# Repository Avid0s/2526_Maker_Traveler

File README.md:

# 25-26_Maker_Traveler
Gabriel VIDON\
Projet d'option Maker à l'ENSEA.

# Vidéo :
Version 1 min 30 :\
https://youtu.be/IOBbxCDs6Es

Version 1 min 45 : (une étape en plus)\
https://youtu.be/CtQkx19j3xo

# 1 Description du projet

## 1.1 Contexte

J'ai toujours été passioné par la robotique et les systèmes embarqués, c'est pour cela que dans le cadre d'un projet Maker qui devait regrouper le plus de technologies possibles pour apprendre leur fonctionnement. J'ai décidé de travailler sur un projet de voiture téléguidée par connection bluetooth. Pour éviter de devoir créer un système de rotation pour les roues de zero, j'ai décidé d'utiliser des roues holonomes.\ 
Ce système qui deverait toucher à toutes les technologies d'impression 3D, de découpe laser, routage pcb, et toutes les autres vues en cours de Maker.
Mes objectifs sont les suivants :
- Créer un chassis pouvant supporter l'ensemble du système
- Créer un PCB avec un ESP32 permettant de controler les moteurs
- Créer un programme permettant de communiquer en bluetooth avec l'ESP et de controler la voiture depuis un telephone puis une manette.

## 1.2 Retroplanning

| Séance | Objectif|
|--------|---------|
|TP1     |Définir les spécifications, choisir les composants, rédiger le cahier des charges et planifier les tâches.|
|TP2     |Modéliser le châssis en 3D, concevoir le schéma du PCB et préparer les fichiers pour la fabrication.|
|TP3     |Imprimer/découper le châssis, finaliser le PCB et préparer les outils pour la séance suivante.|
|TP4     |Souder les composants sur le PCB et écrire le code de base pour contrôler les moteurs.|
|TP5     |Développer la communication Bluetooth et tester les mouvements de la voiture.|
|TP6     |Assembler le châssis, tester l'ensemble (mouvements, Bluetooth) et finaliser le code.|
|TP7     |Valider les tests, rédiger le rapport technique et préparer la démonstration.|

# 2 Projet

## Séance 1

L'alimentation de la voiture sera fait grâce a une batterie 12v, cette tension sera convertie en 5v par un convertisseur DC-DC, qui alimentera toute la carte.\
Un esp32 recuperera les informations de mouvement depuis une connection bluetooth, enverra la PWM appropriée aux drivers, qui eux controleront les moteurs.\
Les moteurs seront eux alimentés par la batterie 12v, et leur valeur d'encodeur sera renvoyée à l'esp pour permettre un niveau de précision adéquat pour utiliser les roues omnidirectionelles.\
Une interface sera faite sur telephone avec l'application BT electronics, et si le temps le permets, le robot sera controlé par une manette de ps4

| Composant | Référence | Lien | Quantité |
|-----------|-----------|------|----------|
| Moteurs | FIT0520 | [https://www.dfrobot.com/product-1619.html](https://www.dfrobot.com/product-1619.html)| x4 |
| Drivers moteur | DRV8411APWPR | | x2 |
| ESP32 | | | x1 |
| Roues omnidirectionelles | FIT0779 | [https://www.gotronic.fr/art-roue-omnidirectionnelle-droite-fit0780-34179.htm](https://www.gotronic.fr/art-roue-omnidirectionnelle-droite-fit0780-34179.htm) | x2L x2R |
| Convertisseur 6v-5v | 171013801 | [https://www.we-online.com/components/products/datasheet/171013801.pdf](https://www.we-online.com/components/products/datasheet/171013801.pdf) | x1 |
| Batterie 6v | fait in ensea |  | x1 |

Lien Onshape :\
[https://cad.onshape.com/documents/018aeca4da422949587763ea/w/2b34d823b7b37a4e9442f19b/e/016c48b2dd776d725fede060](https://cad.onshape.com/documents/018aeca4da422949587763ea/w/2b34d823b7b37a4e9442f19b/e/016c48b2dd776d725fede060)

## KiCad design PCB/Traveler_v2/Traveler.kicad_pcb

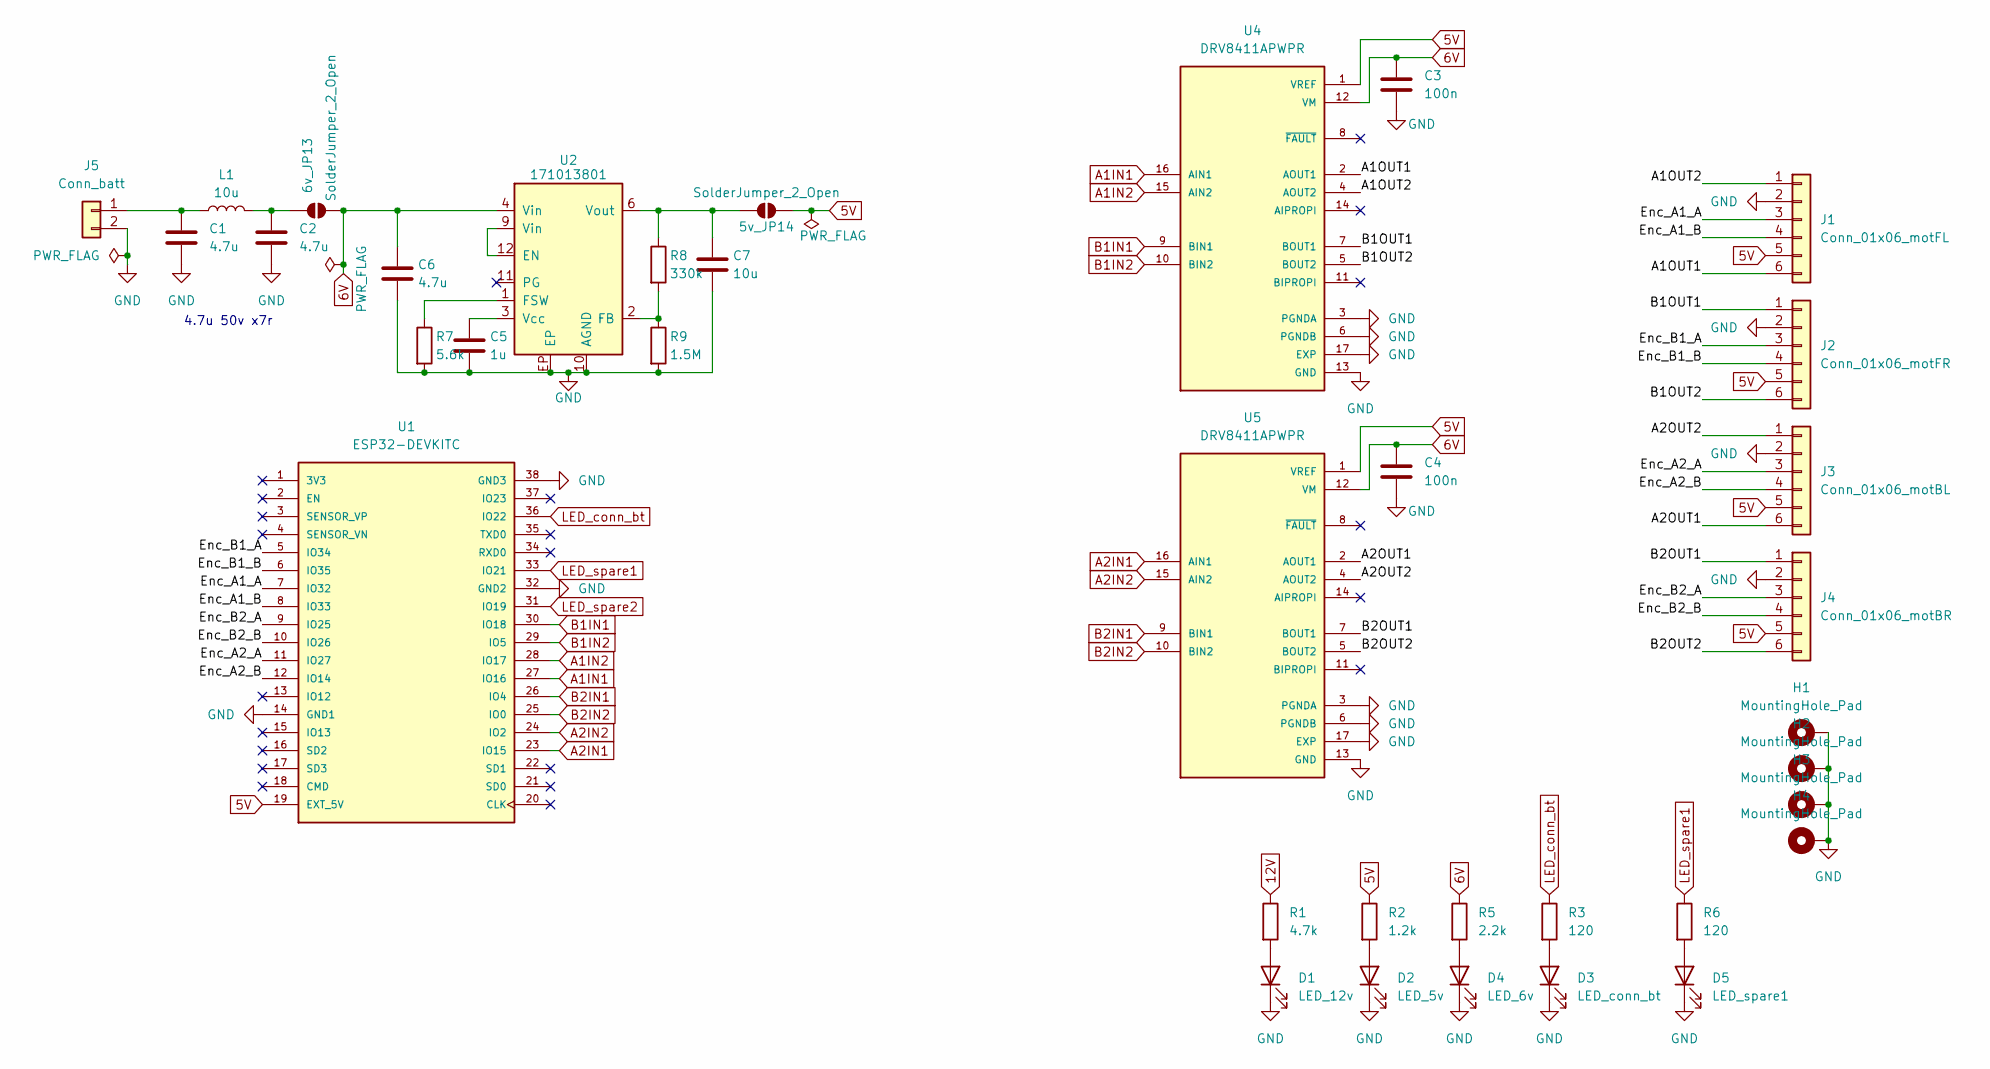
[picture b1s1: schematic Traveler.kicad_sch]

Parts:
5v_JP14, 6v_JP13: SolderJumper_2_Open; SolderJumper-2_P1.3mm_Open_TrianglePad1.0x1.5mm
C1, C2, C6: 4.7u; C_0603_1608Metric
C3, C4: 100n; C_0603_1608Metric
C5: 1u; C_0603_1608Metric
C7: 10u; C_0603_1608Metric
D1: LED_12v; LED_0603_1608Metric_Pad1.05x0.95mm_HandSolder
D2: LED_5v; LED_0603_1608Metric_Pad1.05x0.95mm_HandSolder
D3: LED_conn_bt; LED_0603_1608Metric_Pad1.05x0.95mm_HandSolder
D4: LED_6v; LED_0603_1608Metric_Pad1.05x0.95mm_HandSolder
D5: LED_spare1; LED_0603_1608Metric_Pad1.05x0.95mm_HandSolder
H1, H2, H3, H4: MountingHole_Pad; MountingHole_2.7mm_Pad_TopBottom
J1: Conn_01x06_motFL; PinHeader_1x06_P2.54mm_Vertical
J2: Conn_01x06_motFR; PinHeader_1x06_P2.54mm_Vertical
J3: Conn_01x06_motBL; PinHeader_1x06_P2.54mm_Vertical
J4: Conn_01x06_motBR; PinHeader_1x06_P2.54mm_Vertical
J5: Conn_batt; JST_EH_B2B-EH-A_1x02_P2.50mm_Vertical
L1: 10u; capa1
R1: 4.7k; R_0603_1608Metric
R2: 1.2k; R_0603_1608Metric
R3, R6: 120; R_0603_1608Metric
R5: 2.2k; R_0603_1608Metric
R7: 5.6k; R_0603_1608Metric
R8: 330k; R_0603_1608Metric
R9: 1.5M; R_0603_1608Metric
U1: ESP32-DEVKITC; MODULE_ESP32-DEVKITC; PARTREV N/A
U2: 171013801; WPME-VDLM_LGA-12EP
U4, U5: DRV8411APWPR; IC_DRV8411APWPR; PARTREV A

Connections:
5V: 5v_JP14.2 (B), J1.5, J2.5, J3.5, J4.5, R2.1, U1.19 (EXT_5V), U4.1 (VREF), U5.1 (VREF)
6V: 6v_JP13.2 (B), C3.1, C4.1, C6.1, R5.1, U2.4 (Vin), U2.5 (Vin), U4.12 (VM), U5.12 (VM)
12V: R1.1
/A1OUT1: J1.6, U4.2 (AOUT1)
/A1OUT2: J1.1, U4.4 (AOUT2)
/A2OUT1: J3.6, U5.2 (AOUT1)
/A2OUT2: J3.1, U5.4 (AOUT2)
/B1OUT1: J2.1, U4.7 (BOUT1)
/B1OUT2: J2.6, U4.5 (BOUT2)
/B2OUT1: J4.1, U5.7 (BOUT1)
/B2OUT2: J4.6, U5.5 (BOUT2)
/Enc_A1_A: J1.3, U1.7 (IO32)
/Enc_A1_B: J1.4, U1.8 (IO33)
/Enc_A2_A: J3.3, U1.11 (IO27)
/Enc_A2_B: J3.4, U1.12 (IO14)
/Enc_B1_A: J2.3, U1.5 (IO34)
/Enc_B1_B: J2.4, U1.6 (IO35)
/Enc_B2_A: J4.3, U1.9 (IO25)
/Enc_B2_B: J4.4, U1.10 (IO26)
A1IN1: U1.27 (IO16), U4.16 (AIN1)
A1IN2: U1.28 (IO17), U4.15 (AIN2)
A2IN1: U1.23 (IO15), U5.16 (AIN1)
A2IN2: U1.24 (IO2), U5.15 (AIN2)
B1IN1: U1.30 (IO18), U4.9 (BIN1)
B1IN2: U1.29 (IO5), U4.10 (BIN2)
B2IN1: U1.26 (IO4), U5.9 (BIN1)
B2IN2: U1.25 (IO0), U5.10 (BIN2)
GND: C1.2, C2.2, C3.2, C4.2, C5.2, C6.2, C7.2, D1.1 (K), D2.1 (K), D3.1 (K), D4.1 (K), D5.1 (K), H1.1, H2.1, H3.1, H4.1, J1.2, J2.2, J3.2, J4.2, J5.2, R7.2, R9.2, U1.14 (GND1), U1.32 (GND2), U1.38 (GND3), U2.10 (AGND), U2.EP, U4.3 (PGNDA), U4.6 (PGNDB), U4.13 (GND), U4.17 (EXP), U5.3 (PGNDA), U5.6 (PGNDB), U5.13 (GND), U5.17 (EXP)
LED_conn_bt: R3.1, U1.36 (IO22)
LED_spare1: R6.1, U1.33 (IO21)
LED_spare2: U1.31 (IO19)
unnamed: 6v_JP13.1 (A), C2.1, L1.2
unnamed: D1.2 (A), R1.2
unnamed: D2.2 (A), R2.2
unnamed: D3.2 (A), R3.2
unnamed: D4.2 (A), R5.2
unnamed: D5.2 (A), R6.2
unnamed: C1.1, J5.1, L1.1
unnamed: U2.9 (Vin), U2.12 (EN)
unnamed: R8.2, R9.1, U2.2 (FB)
unnamed: R7.1, U2.1 (FSW)
unnamed: C5.1, U2.3 (Vcc)
Vout: 5v_JP14.1 (A), C7.1, R8.1, U2.6 (Vout), U2.7 (Vout)

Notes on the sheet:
4.7u 50v x7r

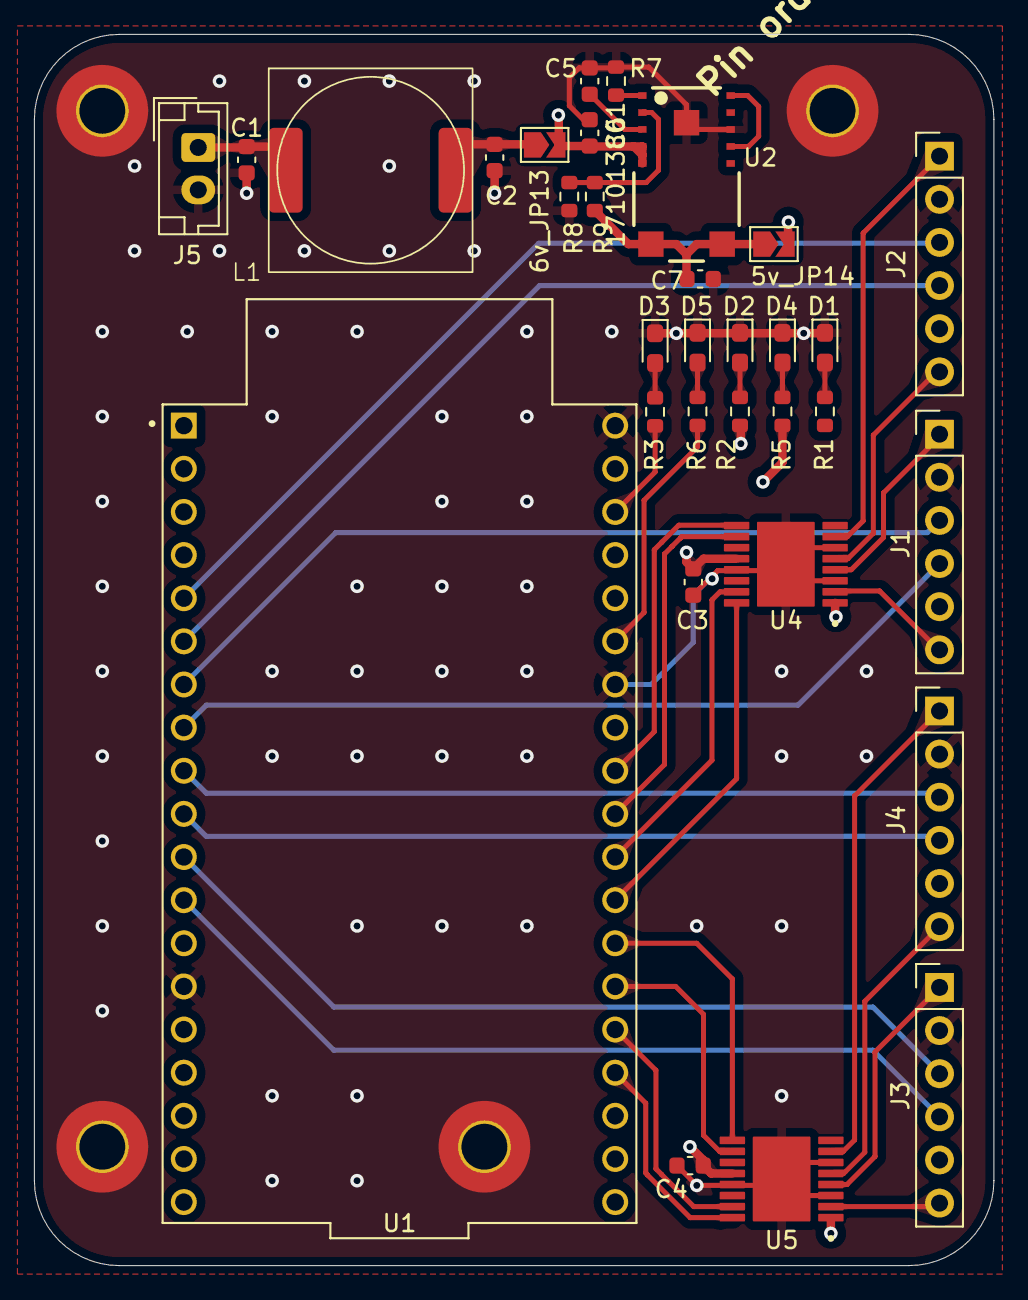
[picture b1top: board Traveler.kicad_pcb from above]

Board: 4 copper layers, 56.5 x 72.5 mm, 36 parts (0 on the bottom side), 41 nets.

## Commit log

2026-01-15 Initial readme txt
2026-01-19 update description
2026-01-19 mise en forme + nom
2026-01-22 added context and retroplanning
2026-01-22 Update project title formatting in README
2026-02-16 Added séance 1
    Added project details including power supply, motor control, and components list.
2026-03-09 added ref driver moteur
2026-03-09 début schéma elec pcb
    recherches sur moteurs, drivers, esp and more
2026-03-19 Finition de pcb, prèt pour verification
2026-03-23 Changed component
2026-03-23 Vers 2 couches
    A créer : une vers 4 couches, remplacer batt 12v vers 6v pour alim directement depuis batt
2026-03-23 changements schematic elec pour une batt 6v
    a faire, routage :(
2026-03-23 Finition PCB et envoi vers fabrication
2026-03-24 fichiers gerber et suppression backups
2026-03-30 cration of cad pcb file
2026-03-30 changement composants vers mot 6V + rajout liens
2026-03-30 lien onshape
2026-04-02 Remove Traveler.cad; add backups, STL, lock
    Delete the large Traveler.cad export and update the KiCad project metadata. Add two backup ZIPs in PCB/Traveler_v2/Traveler-backups, include Traveler.stl and the temporary ~Traveler.kicad_pcb.lck loc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
2026-04-13 erreur avec le ldo, ordre des pins inversé sur KiCad, composant à souder en araignée
2026-04-29 Code moteurs
2026-04-29 prgm, pour de vrai
    code BT et fonctions moteurs
2026-04-29 setup sous projets
2026-04-29 Rename README.me.txt to README.md
2026-04-30 Added onshape screenshots
    Added images of various projects to the README.
2026-04-30 added all project things
2026-04-30 removed unused functions
2026-04-30 added image
2026-05-01 added vid link
2026-05-01 added 1m30 vid
2026-05-01 petites modifs code et kicad
2026-05-01 added couture pics
